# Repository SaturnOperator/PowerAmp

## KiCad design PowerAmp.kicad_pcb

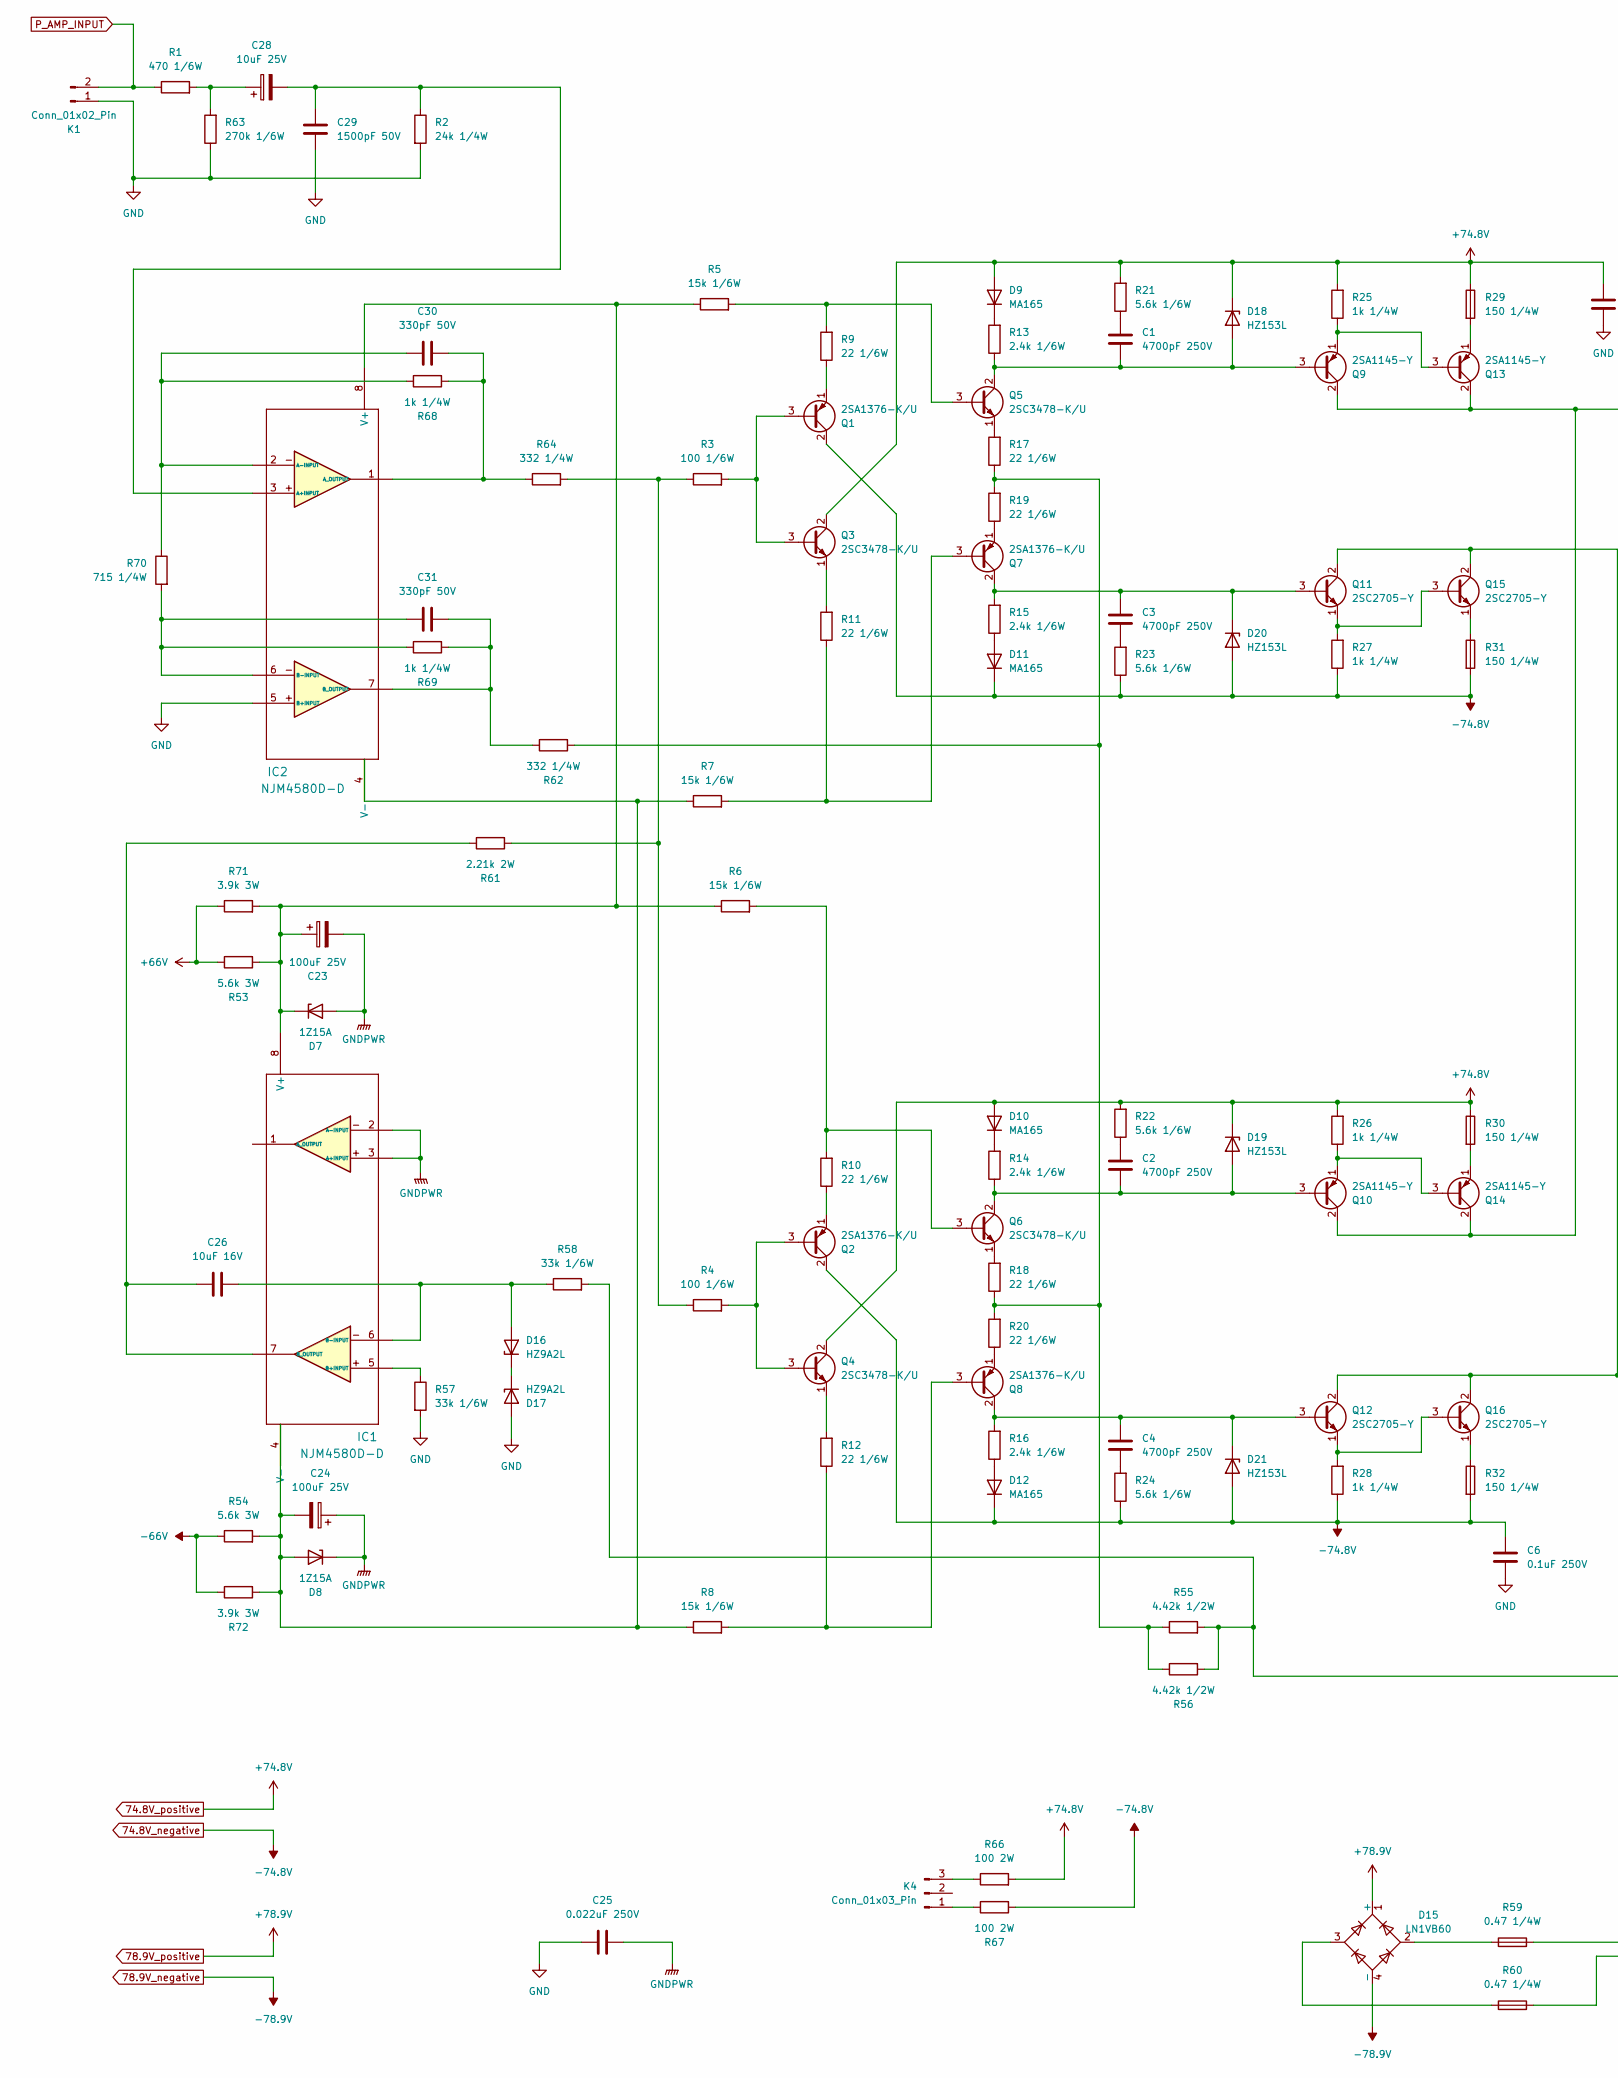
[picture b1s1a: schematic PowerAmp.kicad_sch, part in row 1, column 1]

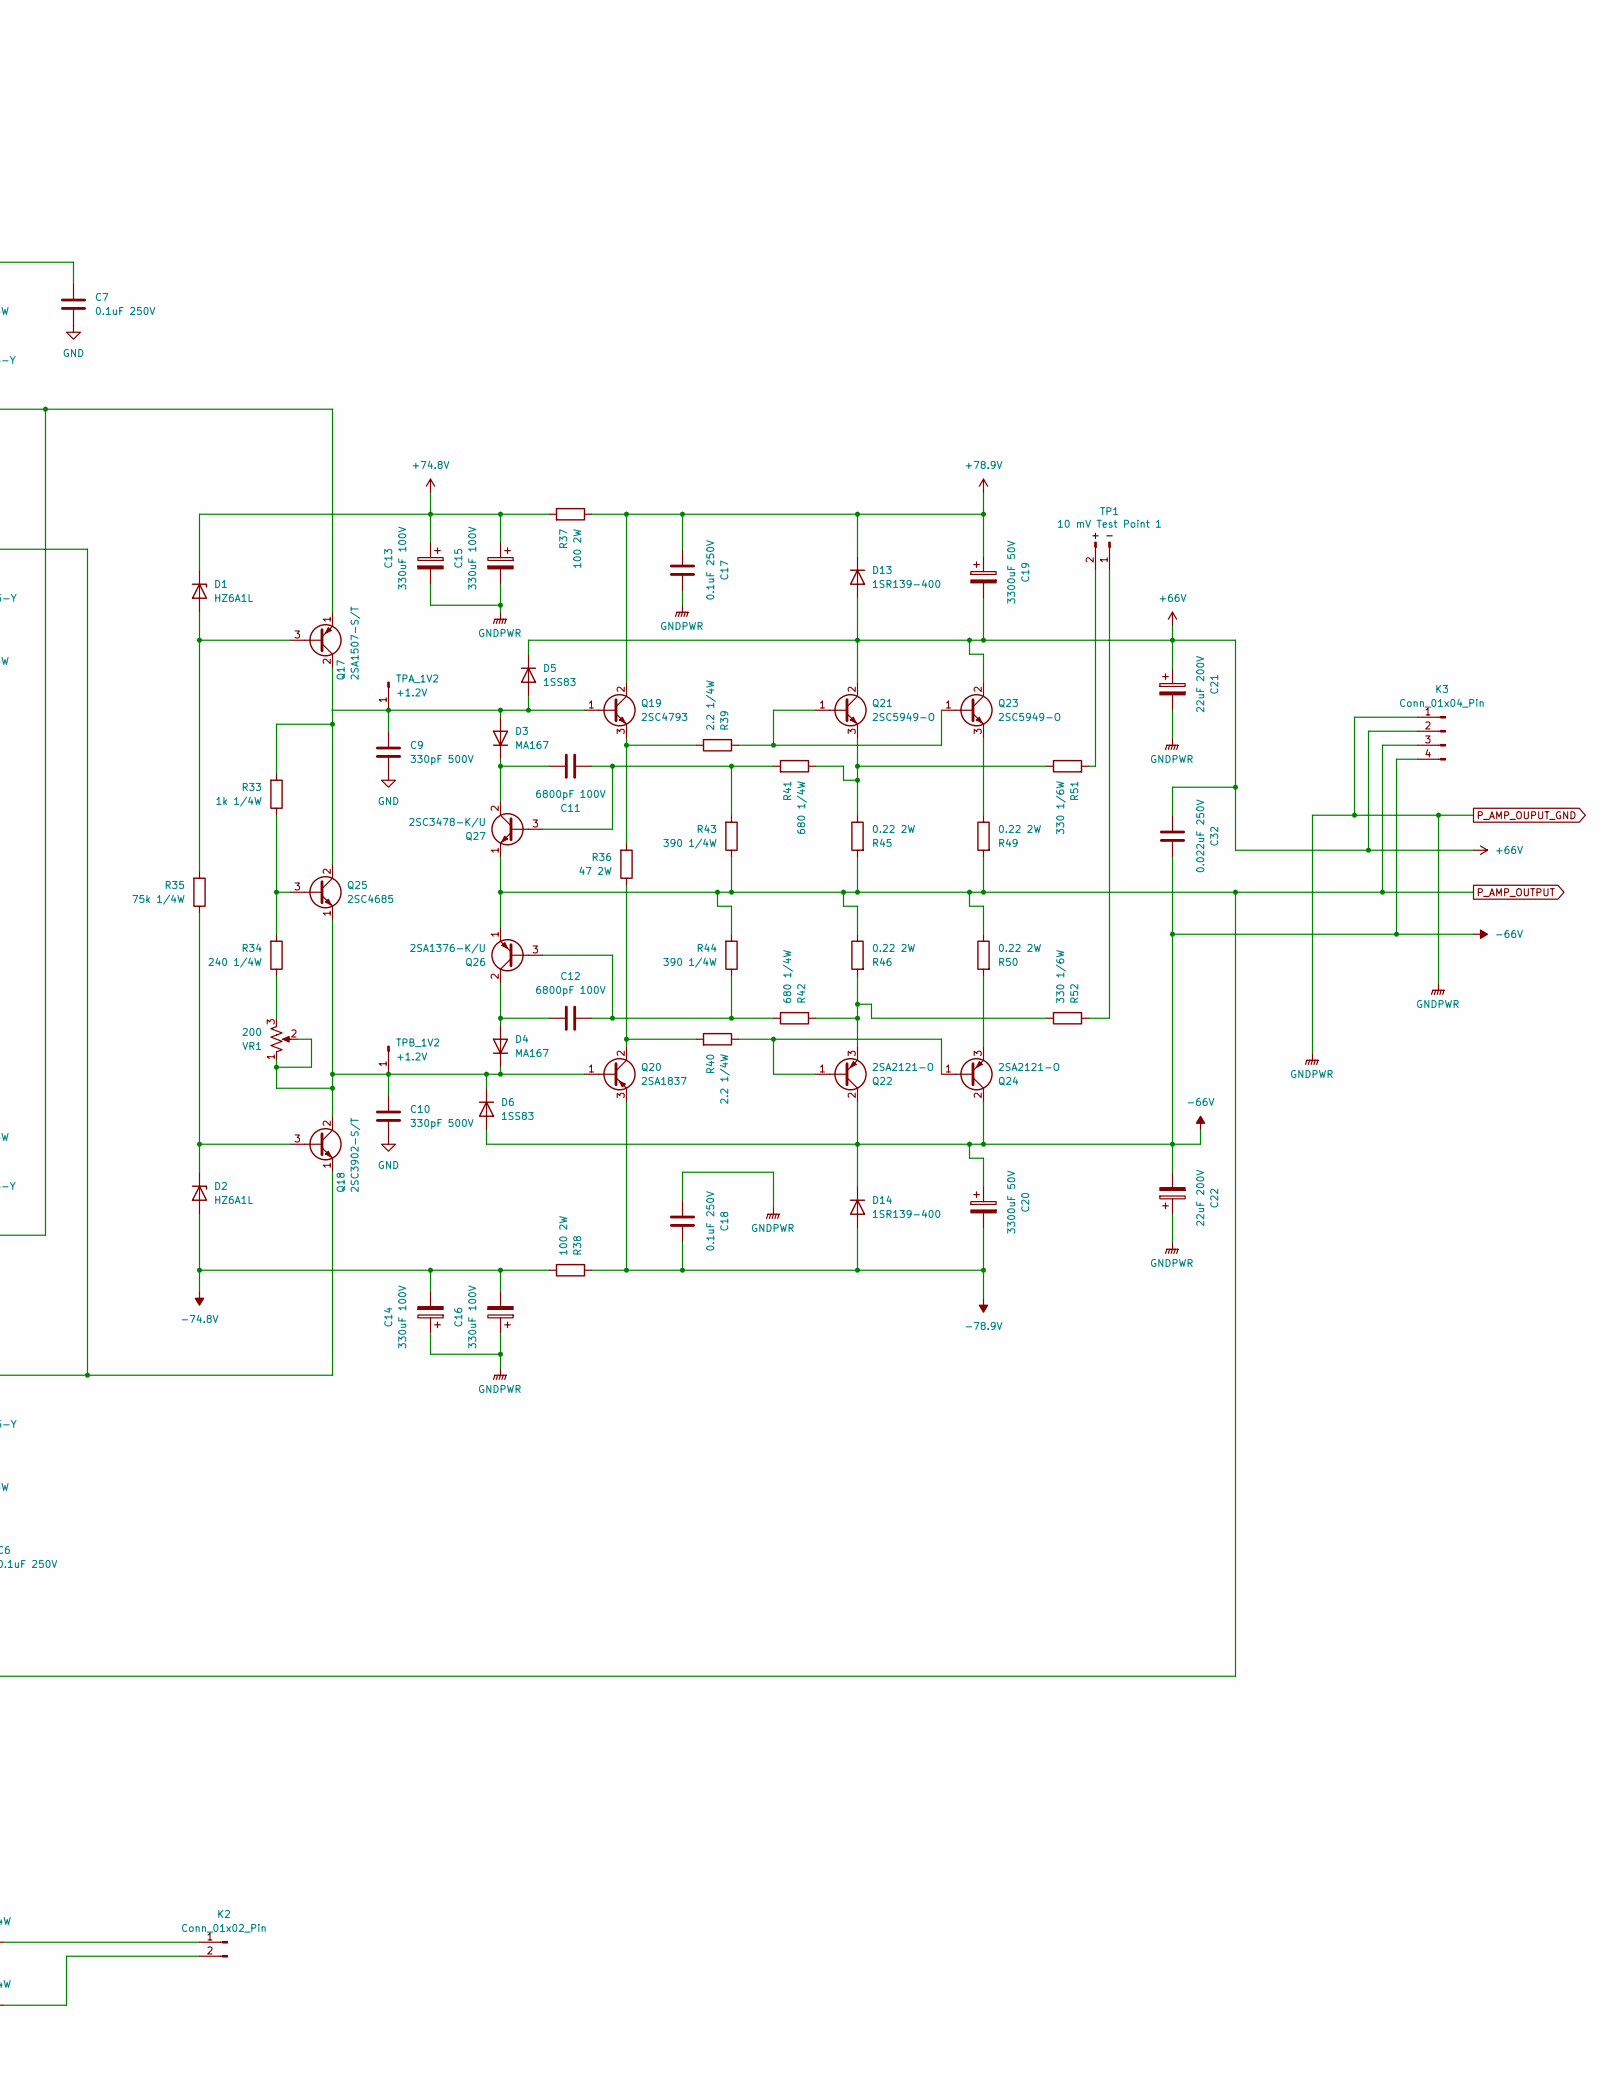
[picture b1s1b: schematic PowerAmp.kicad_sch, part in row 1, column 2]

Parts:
C1, C2, C3, C4: 4700pF 250V; C_Rect_L7.2mm_W5.5mm_P5.00mm_FKS2_FKP2_MKS2_MKP2
C6, C7, C17, C18: 0.1uF 250V; C_Rect_L7.2mm_W4.5mm_P5.00mm_FKS2_FKP2_MKS2_MKP2
C9, C10: 330pF 500V; C_Disc_D5.0mm_W2.5mm_P5.00mm
C11, C12: 6800pF 100V; C_Rect_L7.2mm_W5.5mm_P5.00mm_FKS2_FKP2_MKS2_MKP2
C13, C14, C15, C16: 330uF 100V; CP_Radial_D12.5mm_P5.00mm
C19, C20: 3300uF 50V; CP_Radial_D18.0mm_P7.50mm
C21, C22: 22uF 200V; CP_Radial_D10.0mm_P5.00mm
C23, C24: 100uF 25V; CP_Radial_D8.0mm_P3.50mm
C25, C32: 0.022uF 250V; C_Rect_L7.2mm_W3.0mm_P5.00mm_FKS2_FKP2_MKS2_MKP2
C26: 10uF 16V; CP_Radial_D8.0mm_P3.50mm
C28: 10uF 25V; CP_Radial_D8.0mm_P3.50mm
C29: 1500pF 50V; C_Rect_L7.2mm_W4.5mm_P5.00mm_FKS2_FKP2_MKS2_MKP2
C30, C31: 330pF 50V; C_Rect_L7.2mm_W4.5mm_P5.00mm_FKS2_FKP2_MKS2_MKP2
D1, D2: HZ6A1L; D_A-405_P7.62mm_Horizontal
D3, D4: MA167; D_A-405_P7.62mm_Horizontal
D5, D6: 1SS83; D_A-405_P7.62mm_Horizontal
D7, D8: 1Z15A; D_A-405_P7.62mm_Horizontal
D9, D10, D11, D12: MA165; D_A-405_P7.62mm_Horizontal
D13, D14: 1SR139-400; D_A-405_P7.62mm_Horizontal
D15: LN1VB60; Diode_Bridge_19.0x3.5x10.0mm_P5.0mm
D16, D17: HZ9A2L; D_A-405_P7.62mm_Horizontal
D18, D19, D20, D21: HZ153L; D_A-405_P7.62mm_Horizontal
IC1, IC2: NJM4580D-D; DIP-8_W7.62mm
K1, K2: Conn_01x02_Pin; PinSocket_1x02_P2.54mm_Vertical
K3: Conn_01x04_Pin; PinSocket_1x04_P2.54mm_Vertical
K4: Conn_01x03_Pin; PinSocket_1x03_P2.54mm_Vertical
Q1, Q2, Q7, Q8, Q26: 2SA1376-K/U; TO-92_Inline
Q3, Q4, Q5, Q6, Q27: 2SC3478-K/U; TO-92_Inline
Q9, Q10, Q13, Q14: 2SA1145-Y; TO-92_Inline
Q11, Q12, Q15, Q16: 2SC2705-Y; TO-92_Inline
Q17: 2SA1507-S/T; TO-126-3_Vertical
Q18: 2SC3902-S/T; TO-126-3_Vertical
Q19: 2SC4793; TO-220-3_Vertical
Q20: 2SA1837; TO-220-3_Vertical
Q21, Q23: 2SC5949-O; TO-3P-3_Vertical
Q22, Q24: 2SA2121-O; TO-3P-3_Vertical
Q25: 2SC4685; TO-126-3_Vertical
R1: 470 1/6W; R_Axial_DIN0207_L6.3mm_D2.5mm_P10.16mm_Horizontal
R2: 24k 1/4W; R_Axial_DIN0207_L6.3mm_D2.5mm_P10.16mm_Horizontal
R3, R4: 100 1/6W; R_Axial_DIN0207_L6.3mm_D2.5mm_P10.16mm_Horizontal
R5, R6, R7, R8: 15k 1/6W; R_Axial_DIN0207_L6.3mm_D2.5mm_P10.16mm_Horizontal
R9, R10, R11, R12, R17, R18, R19, R20: 22 1/6W; R_Axial_DIN0207_L6.3mm_D2.5mm_P10.16mm_Horizontal
R13, R14, R15, R16: 2.4k 1/6W; R_Axial_DIN0207_L6.3mm_D2.5mm_P10.16mm_Horizontal
R21, R22, R23, R24: 5.6k 1/6W; R_Axial_DIN0207_L6.3mm_D2.5mm_P10.16mm_Horizontal
R25, R26, R27, R28, R33: 1k 1/4W; R_Axial_DIN0207_L6.3mm_D2.5mm_P10.16mm_Horizontal
R29, R30, R31, R32: 150 1/4W; R_Axial_DIN0207_L6.3mm_D2.5mm_P10.16mm_Horizontal
R34: 240 1/4W; R_Axial_DIN0207_L6.3mm_D2.5mm_P10.16mm_Horizontal
R35: 75k 1/4W; R_Axial_DIN0207_L6.3mm_D2.5mm_P10.16mm_Horizontal
R36: 47 2W; R_Axial_DIN0414_L11.9mm_D4.5mm_P15.24mm_Horizontal
R37, R38, R66, R67: 100 2W; R_Axial_DIN0414_L11.9mm_D4.5mm_P15.24mm_Horizontal
R39, R40: 2.2 1/4W; R_Axial_DIN0207_L6.3mm_D2.5mm_P10.16mm_Horizontal
R41, R42: 680 1/4W; R_Axial_DIN0207_L6.3mm_D2.5mm_P10.16mm_Horizontal
R43, R44: 390 1/4W; R_Axial_DIN0207_L6.3mm_D2.5mm_P10.16mm_Horizontal
R45, R46, R49, R50: 0.22 2W; R_Box_L14.0mm_W5.0mm_P9.00mm
R51, R52: 330 1/6W; R_Axial_DIN0207_L6.3mm_D2.5mm_P10.16mm_Horizontal
R53, R54: 5.6k 3W; R_Axial_DIN0617_L17.0mm_D6.0mm_P20.32mm_Horizontal
R55, R56: 4.42k 1/2W; R_Axial_DIN0411_L9.9mm_D3.6mm_P15.24mm_Horizontal
R57, R58: 33k 1/6W; R_Axial_DIN0207_L6.3mm_D2.5mm_P10.16mm_Horizontal
R59, R60: 0.47 1/4W; R_Axial_DIN0207_L6.3mm_D2.5mm_P10.16mm_Horizontal
R61: 2.21k 2W; R_Axial_DIN0617_L17.0mm_D6.0mm_P20.32mm_Horizontal
R62, R64: 332 1/4W; R_Axial_DIN0411_L9.9mm_D3.6mm_P15.24mm_Horizontal
R63: 270k 1/6W; R_Axial_DIN0207_L6.3mm_D2.5mm_P10.16mm_Horizontal
R68, R69: 1k 1/4W; R_Axial_DIN0204_L3.6mm_D1.6mm_P7.62mm_Horizontal
R70: 715 1/4W; R_Axial_DIN0204_L3.6mm_D1.6mm_P7.62mm_Horizontal
R71, R72: 3.9k 3W; R_Axial_DIN0617_L17.0mm_D6.0mm_P20.32mm_Horizontal
TP1: 10 mV Test Point 1; PinHeader_1x02_P2.54mm_Vertical
TPA_1V2: +1.2V; PinHeader_1x01_P2.54mm_Vertical
TPB_1V2: +1.2V; PinHeader_1x01_P2.54mm_Vertical
VR1: 200; Potentiometer_ACP_CA6-H2,5_Horizontal

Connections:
74.8V_negative: C6.1, C14.2, C16.2, D2.2 (A), D11.1 (K), D12.1 (K), D20.2 (A), D21.2 (A), Q1.2 (C), Q2.2 (C), R23.1, R24.1, R27.1, R28.1, R31.2, R32.2, R38.1, R67.2
74.8V_positive: C7.1, C13.1, C15.1, D1.1 (K), D9.2 (A), D10.2 (A), D18.1 (K), D19.1 (K), Q3.2 (C), Q4.2 (C), R21.2, R22.2, R25.2, R26.2, R29.1, R30.1, R37.2, R66.2
78.9V_negative: C18.2, C20.2, D14.2 (A), D15.4 (-), Q20.3 (E), R38.2
78.9V_positive: C17.1, C19.1, D13.1 (K), D15.1 (+), Q19.2 (C), R37.1
+66V: C19.2, C21.1, C32.1, D5.1 (K), D13.2 (A), K3.2, Q21.2 (C), Q23.2 (C), R53.1, R71.1
-66V: C20.1, C22.2, C32.2, D6.2 (A), D14.1 (K), K3.4, Q22.2 (C), Q24.2 (C), R54.1, R72.1
GND: C6.2, C7.2, C9.2, C10.2, C25.1, C29.2, D17.2 (A), IC2.5 (B+INPUT), K1.1, R2.2, R57.2, R63.1
unnamed: C1.1, R21.1
unnamed: C2.1, R22.1
unnamed: C3.2, R23.2
unnamed: C4.2, R24.2
unnamed: C28.1, R1.2, R63.2
unnamed: D1.2 (A), Q17.3 (B), R35.2
unnamed: D2.1 (K), Q18.3 (B), R35.1
unnamed: C9.1, D3.2 (A), D5.2 (A), Q19.1 (B), TPA_1V2.1 (Pin_1_1)
unnamed: C11.2, D3.1 (K), Q27.2 (C)
unnamed: C12.1, D4.2 (A), Q26.2 (C)
unnamed: C10.1, D4.1 (K), D6.1 (K), Q18.2 (C), Q20.1 (B), Q25.1 (E), TPB_1V2.1 (Pin_1_1), VR1.1, VR1.2
unnamed: C23.1, D7.1 (K), IC1.8 (V+), IC2.8 (V+), R5.1, R6.1, R53.2, R71.2
unnamed: C24.2, D8.2 (A), IC1.4 (V-), IC2.4 (V-), R7.1, R8.1, R54.2, R72.2
unnamed: D9.1 (K), R13.2
unnamed: D10.1 (K), R14.2
unnamed: D11.2 (A), R15.1
unnamed: D12.2 (A), R16.1
unnamed: D15.2, R59.1
unnamed: D15.3, R60.1
unnamed: C26.1, D16.2 (A), IC1.6 (B-INPUT), R58.1
unnamed: D16.1 (K), D17.1 (K)
unnamed: C1.2, D18.2 (A), Q5.2 (C), Q9.3 (B), R13.1
unnamed: C2.2, D19.2 (A), Q6.2 (C), Q10.3 (B), R14.1
unnamed: C3.1, D20.1 (K), Q7.2 (C), Q11.3 (B), R15.2
unnamed: C4.1, D21.1 (K), Q8.2 (C), Q12.3 (B), R16.2
unnamed: IC1.5 (B+INPUT), R57.1
unnamed: C26.2, IC1.7 (B_OUTPUT), R61.1
unnamed: C28.2, C29.1, IC2.3 (A+INPUT), R2.1
unnamed: C30.1, IC2.2 (A-INPUT), R68.1, R70.1
unnamed: C30.2, IC2.1 (A_OUTPUT), R64.1, R68.2
unnamed: C31.1, IC2.6 (B-INPUT), R69.1, R70.2
unnamed: C31.2, IC2.7 (B_OUTPUT), R62.1, R69.2
unnamed: K2.1, R59.2
unnamed: K2.2, R60.2
unnamed: K4.1, R67.1
unnamed: K4.3, R66.1
unnamed: Q1.3 (B), Q3.3 (B), R3.2
unnamed: Q1.1 (E), R9.1
unnamed: Q2.3 (B), Q4.3 (B), R4.2
unnamed: Q2.1 (E), R10.1
unnamed: Q3.1 (E), R11.2
unnamed: Q4.1 (E), R12.2
unnamed: Q5.3 (B), R5.2, R9.2
unnamed: Q5.1 (E), R17.2
unnamed: Q6.3 (B), R6.2, R10.2
unnamed: Q6.1 (E), R18.2
unnamed: Q7.3 (B), R7.2, R11.1
unnamed: Q7.1 (E), R19.1
unnamed: Q8.3 (B), R8.2, R12.1
unnamed: Q8.1 (E), R20.1
unnamed: Q9.2 (C), Q10.2 (C), Q13.2 (C), Q14.2 (C), Q17.1 (E)
unnamed: Q10.1 (E), Q14.3 (B), R26.1
unnamed: Q11.2 (C), Q12.2 (C), Q15.2 (C), Q16.2 (C), Q18.1 (E)
unnamed: Q11.1 (E), Q15.3 (B), R27.2
unnamed: Q12.1 (E), Q16.3 (B), R28.2
unnamed: Q9.1 (E), Q13.3 (B), R25.1
unnamed: Q13.1 (E), R29.2
unnamed: Q14.1 (E), R30.2
unnamed: Q15.1 (E), R31.1
unnamed: Q16.1 (E), R32.1
unnamed: Q17.2 (C), Q25.2 (C), R33.2
unnamed: Q19.3 (E), R36.2, R39.1
unnamed: Q20.2 (C), R36.1, R40.2
unnamed: Q21.1 (B), Q23.1 (B), R39.2
unnamed: Q21.3 (E), R41.1, R45.1, R51.1
unnamed: Q22.1 (B), Q24.1 (B), R40.1
unnamed: Q22.3 (E), R42.2, R46.2, R52.1
unnamed: Q23.3 (E), R49.1
unnamed: Q24.3 (E), R50.2
unnamed: Q25.3 (B), R33.1, R34.2
unnamed: C12.2, Q26.3 (B), R42.1, R44.1
unnamed: C11.1, Q27.3 (B), R41.2, R43.2
unnamed: R3.1, R4.1, R61.2, R64.2
unnamed: R17.1, R18.1, R19.2, R20.2, R55.1, R56.1, R62.2
unnamed: R34.1, VR1.3
unnamed: R52.2, TP1.1
unnamed: R51.2, TP1.2
P_AMP_INPUT: K1.2, R1.1
P_AMP_OUPUT_GND: C13.2, C14.1, C15.2, C16.1, C17.2, C18.1, C21.2, C22.1, C23.2, C24.1, C25.2, D7.2 (A), D8.1 (K), IC1.2 (A-INPUT), IC1.3 (A+INPUT), K3.1
P_AMP_OUTPUT: K3.3, Q26.1 (E), Q27.1 (E), R43.1, R44.2, R45.2, R46.1, R49.2, R50.1, R55.2, R56.2, R58.2

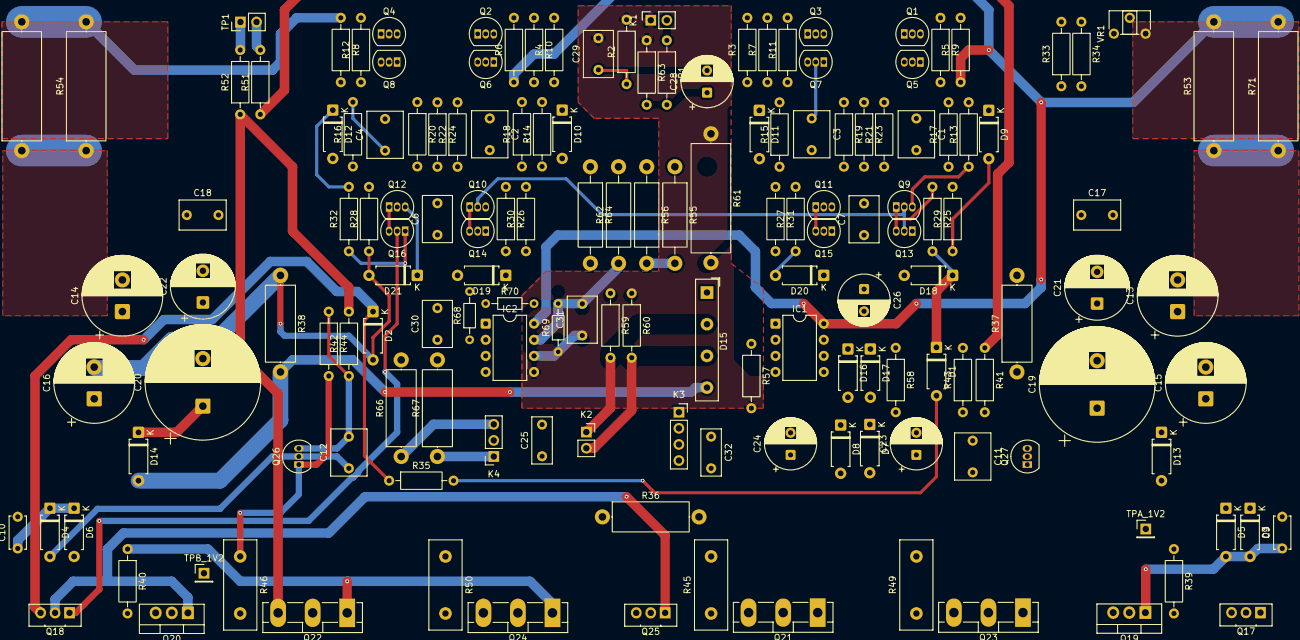
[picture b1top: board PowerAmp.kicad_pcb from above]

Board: 2 copper layers, 156 parts (0 on the bottom side), 87 nets.

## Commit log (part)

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2026-06-07 Power Amp Schematic
